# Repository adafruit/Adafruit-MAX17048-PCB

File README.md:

## Adafruit MAX17048 LiPoly / LiIon Fuel Gauge and Battery Monitor PCB

<a href="http://www.adafruit.com/products/5580"><br/>
Click here to purchase one from the Adafruit shop</a>

PCB files for the Adafruit MAX17048 LiPoly / LiIon Fuel Gauge and Battery Monitor. 

Format is EagleCAD schematic and board layout
* https://www.adafruit.com/product/5580

### Description

Low cost Lithium Polymer batteries have revolutionized electronics - they're thin, they're light, they can be regulated down to 3.3V and they're easy to charge. On your phone, there's a little image of a battery cell that tells you the percentage of charge - so you know when you absolutely need to plug it in and when you can stay untethered.

The Adafruit MAX17048 LiPoly / LiIon Fuel Gauge and Battery Monitor does the same thing. Connect it to your Lipoly or LiIon battery and it will let you know the voltage of the cell, it does the annoying math of decoding the non-linear voltage to get you a valid percentage as well!

Since this nice chip is I2C, it works with any and all microcontroller or microcomputer boards, from the Arduino UNO up to the Raspberry Pi. And you don't have to worry about logic level, as the gauge runs with 3.3V or 5.0V power and logic equally fine.

To use, connect a 1S 3.7-4.2V Lithium Ion or Polymer battery to one of the JST 2 PH ports (either one). Then use the included JST PH jumper cable to connect to your boost converter, Feather, whatever! Use the I2C interface and our Arduino or CircuitPython/Python library code to read the voltage and percentage whenever you like. There are various alerts, low power modes that can be customized as desired.

To get you going fast, we spun up a custom-made PCB in the STEMMA QT form factor, making it easy to interface with. The STEMMA QT connectors on either side are compatible with the SparkFun Qwiic I2C connectors. This allows you to make solderless connections between your development board and the MAX17048 or to chain it with a wide range of other sensors and accessories using a compatible cable. QT Cable is not included, but we have a variety in the shop

### License

Adafruit invests time and resources providing this open source design, please support Adafruit and open-source hardware by purchasing products from [Adafruit](https://www.adafruit.com)!

Designed by Limor Fried/Ladyada for Adafruit Industries.

Creative Commons Attribution/Share-Alike, all text above must be included in any redistribution. 
See license.txt for additional details.

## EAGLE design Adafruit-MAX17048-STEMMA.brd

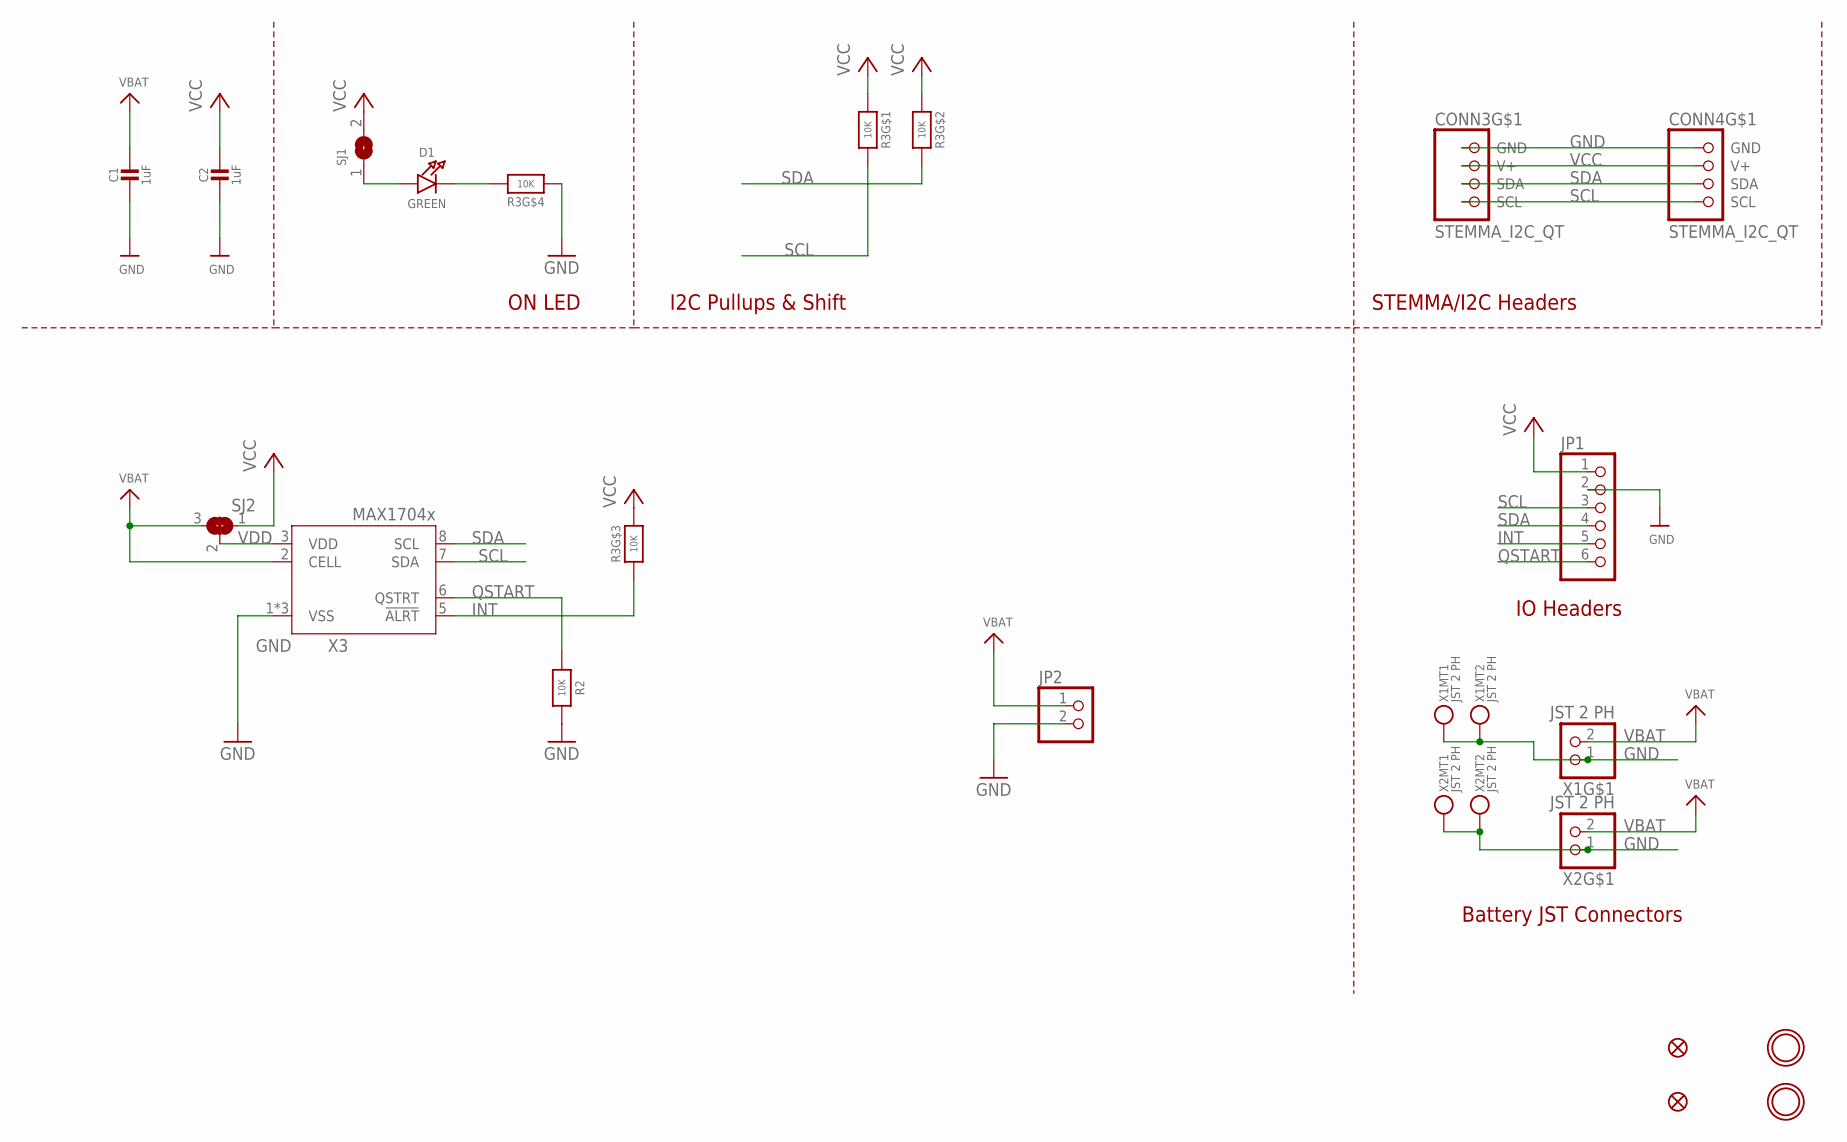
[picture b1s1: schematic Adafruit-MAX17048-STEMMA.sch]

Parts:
C1, C2: 1uF; 0603-NO
CONN3, CONN4: STEMMA_I2C_QT; JST_SH4
D1: GREEN; CHIPLED_0603_NOOUTLINE
FID3, FID4: FIDUCIAL_1MM
JP1: HEADER-1X670MIL; 1X06_ROUND_70
JP2: HEADER-1X2ROUND; 1X02_ROUND
R2: 10K; 0603-NO
R3: 10K; RESPACK_4X0603
SJ1: SOLDERJUMPERCLOSED; SOLDERJUMPER_CLOSEDWIRE
SJ2: SOLDERJUMPER_2WAY; SOLDERJUMPER_2WAY_OPEN_NOPASTE
U$19, U$21: MOUNTINGHOLE2.5; MOUNTINGHOLE_2.5_PLATED
X1, X2: JST 2 PH; JSTPH2_BATT
X3: MAX17048/T; TDFN8_2X2MM

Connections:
GND: C1.2, C2.2, CONN3.1 (GND), CONN4.1 (GND), JP1.2, JP2.2, R2.2, R3.4 (1), X1.1, X1.NC1, X1.NC2, X2.1, X2.NC1, X2.NC2, X3.1 (VSS), X3.4 (VSS), X3.THERMAL (VSS)
INT: JP1.5, R3.3 (1), X3.5 (!ALRT)
unnamed: D1.C, R3.5 (2)
unnamed: D1.A, SJ1.1
QSTART: JP1.6, R2.1, X3.6 (QSTRT)
SCL: CONN3.4 (SCL), CONN4.4 (SCL), JP1.3, R3.8 (2), X3.7 (SDA)
SDA: CONN3.3 (SDA), CONN4.3 (SDA), JP1.4, R3.7 (2), X3.8 (SCL)
VBAT: C1.1, JP2.1, SJ2.3, X1.2, X2.2, X3.2 (CELL)
VCC: C2.1, CONN3.2 (V+), CONN4.2 (V+), JP1.1, R3.1, R3.2 (1), R3.6 (2), SJ1.2, SJ2.1
VDD: SJ2.2, X3.3 (VDD)

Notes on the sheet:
I2C Pullups & Shift
STEMMA/I2C Headers
ON LED
Battery JST Connectors
IO Headers

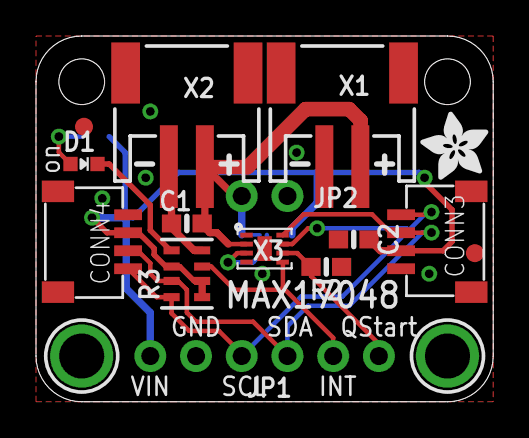
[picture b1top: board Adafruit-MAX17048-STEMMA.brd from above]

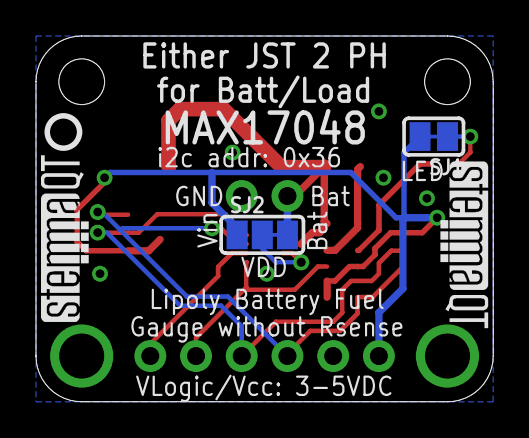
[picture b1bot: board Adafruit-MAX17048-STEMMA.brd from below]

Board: 2 copper layers, 25.4 x 20.3 mm, 22 parts (5 on the bottom side), 10 nets.

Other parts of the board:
U$22: ADAFRUIT_3.5MM
U$25: PCBFEAT-REV-040
U$30, U$31: STEMMAQT

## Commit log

2022-08-31 Adding cookiecutter output

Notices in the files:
parts and their libraries:
microbuilder: This work is placed in the public domain, and may be freely used for commercial and non-commercial work with the following conditions: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
